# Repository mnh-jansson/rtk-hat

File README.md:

# RTK-HAT
Raspberry Pi compatible expansion board for RTK GNSS Module PX1125R

# About
**DISCLAIMER**

**Work In Progress**

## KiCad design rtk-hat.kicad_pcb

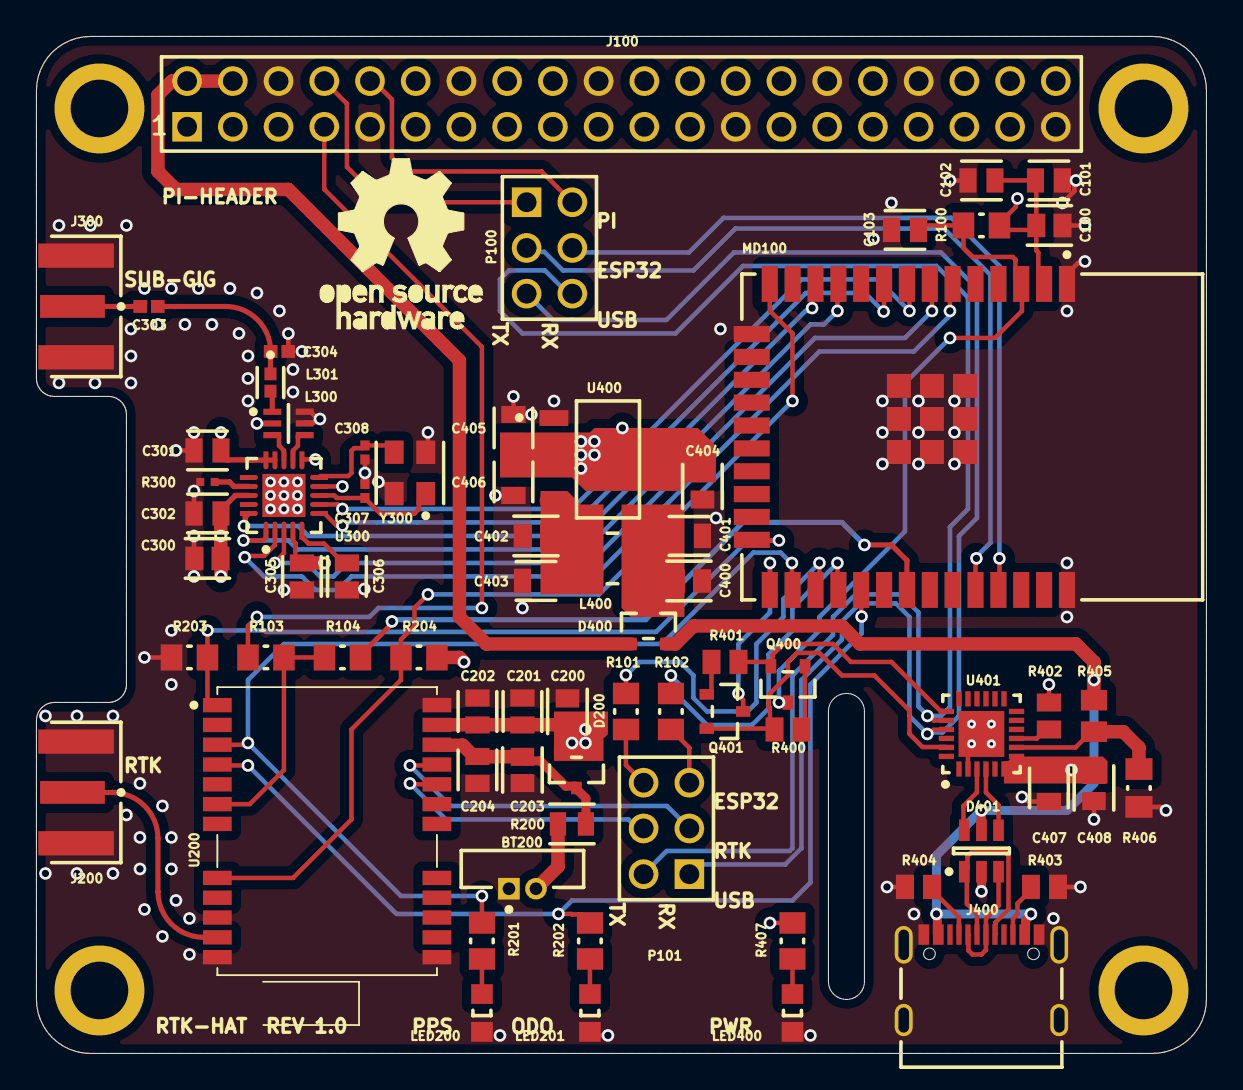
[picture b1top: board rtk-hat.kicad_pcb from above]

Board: 4 copper layers, 65.0 x 56.5 mm, 70 parts (0 on the bottom side), 60 nets.

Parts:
BT200: ML-621S/DN; FP-ML-621S-DN-MFG
C100, C200, C203, C300, C400, C402, C404, C408: GRM21BR61E106KA73L; FP-GRM21B-0_15-IPC_C
C101, C102, C103, C201, C202, C204, C301, C302, C305, C306, C401, C403, C405, C406, C407: C0805C104K5RACTU; FP-C0805C-DN-MFG
C303: GRM1555C1H101JA01D; CAPC1005X55X25ML05T10
C304: GRM1555C1H1R8CA01D; CAPC1005X55X25ML05T10
C307, C308: GRM1555C1H270JA01D; CAPC1005X55X25LL05T10
D200, D400: BAT54C,215; FP-SOT23-MFG
D401: USBLC6-2SC6; STM-SOT23-6L_V
J100: 61304021121
J200, J300: SMA-J-P-H-ST-EM1; FP-SMA-J-P-H-ST-EM1-MFG
J400: 629722000214
L300: 0896BM15A0001E; FP-0896BM15A0001E-MFG
L301: LQG15HN5N6S02D; FP-LQG15HH_02-IPC_A
L400: CBC3225T100MR; FP-CB3225-IPC_A
LED200, LED201, LED400: 150080RS75000; 0805_A
MD100: ESP32-WROOM-32; FP-ESP32-WROOM-32-MFG
P100, P101: 61300621121
Q400, Q401: SS8050-G; FP-SS8050-G-MFG
R100, R101, R102, R103, R104, R201, R202, R203, R204, R407: RC0805FR-071KL; RESC2013X60X35ML10T20
R200: CRGCQ0805F390R; FP-CRGCQ0805-IPC_C
R300: CRCW040256K0FKED; RESC1005X40X25LL05T05
R400, R401, R402, R403, R404: ERA6AEB512V; RESC2013X60X40LL20T25
R405: ERJ-6ENF2212V; RESC2013X70X40NL20T20
R406: CRCW080547K5FKEA; FP-CRCW0805-e3-IPC_A
U200: PX1125R
U300: CC1100ERTKR; FP-RTK0020B-MFG
U400: LDL1117S33R; FP-SOT223-0046067-IPC_C
U401: CP2102N-A01-GQFN24; SLAB-QFN-24-2550x2550TP_A_V
Y300: ABM8-26.000MHZ-10-1-U-T; FP-ABM8-MFG

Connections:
1PPS: MD100.26, R201.2, U200.3
+5V_PI: D400.1, J100.2, J100.4
BOOT_SEL: MD100.24, R203.2, U200.1
GND: BT200.1, C100.2, C101.1, C102.1, C103.2, C200.2, C201.1, C202.1, C203.2, C204.1, C300.2, C301.1, C302.1, C304.1, C305.1, C306.1, C307.1, C308.1, C400.2, C401.1, C402.2, C403.1, C404.2, C405.1, C406.1, C407.1, C408.2, D401.2, J100.6, J100.9, J100.14, J100.20, J100.25, J100.30, J100.34, J100.39, J200.2, J200.3, J200.4, J200.5, J300.2, J300.3, J300.4, J300.5, J400.A1/B12, J400.A12/B1, J400.Shell, L300.2, L300.5, L300.6, LED200.1, LED201.1, LED400.1, MD100.1, MD100.15, MD100.38, MD100.39, R203.1, R300.2, R403.1, R404.1, R406.1, U200.10, U200.12, U200.13, U200.24, U300.16, U300.19, U300.21, U400.1, U401.2, U401.25, Y300.2, Y300.4
NetBT200_2: BT200.2, R200.1
NetC103_1: C103.1, MD100.3, Q400.3, R100.1
NetC203_1: C203.1, C204.2, D200.3, R200.2, U200.22
NetC303_1: C303.1, J300.1
NetC303_2: C303.2, C304.2, L301.1
NetC306_2: C306.2, U300.5
NetC307_2: C307.2, U300.8, Y300.1
NetC308_2: C308.2, U300.10, Y300.3
NetC400_1: C400.1, C401.2, D400.3, L400.1
NetC402_1: C402.1, C403.2, L400.2, U400.3
NetD401_1: D401.1, J400.A6, J400.B6
NetD401_3: D401.3, J400.A7, J400.B7
NetD401_4: D401.4, U401.4
NetD401_6: D401.6, U401.3
NetJ100_7: J100.7, R103.1
NetJ100_8: J100.8, P100.1
NetJ100_10: J100.10, P100.2
NetJ200_1: J200.1, U200.11
NetJ400_A5: J400.A5, R404.2
NetJ400_B5: J400.B5, R403.2
NetL300_1: L300.1, L301.2
NetL300_3: L300.3, U300.13
NetL300_4: L300.4, U300.12
NetLED200_2: LED200.2, R201.1
NetLED201_2: LED201.2, R202.1
NetLED400_2: LED400.2, R407.1
NetMD100_6: MD100.6, U300.2
NetMD100_7: MD100.7, U300.3
NetMD100_8: MD100.8, U300.7
NetMD100_9: MD100.9, U300.6
NetMD100_11: MD100.11, U300.1
NetMD100_12: MD100.12, U300.20
NetMD100_25: MD100.25, Q401.3
NetMD100_27: MD100.27, R101.2
NetMD100_28: MD100.28, R102.2
NetMD100_31: MD100.31, R104.2
NetMD100_34: MD100.34, P100.3
NetMD100_35: MD100.35, P100.4
NetP100_5: P100.5, P101.1, U401.21
NetP100_6: P100.6, P101.2, U401.20
NetP101_5: P101.5, R102.1
NetP101_6: P101.6, R101.1
NetQ400_1: Q400.1, R400.1
NetQ400_2: Q400.2, R401.2, U401.19
NetQ401_1: Q401.1, R401.1
NetQ401_2: Q401.2, R400.2, U401.23
NetR300_1: R300.1, U300.17
NetR402_1: R402.1, U401.9
NetR405_1: R405.1, R406.2, U401.8
ODO: MD100.29, R202.2, U200.4
RSTN: MD100.14, R204.1, U200.8
RXD: P101.3, U200.21
RXD2: R103.2, R104.1, U200.6
TXD: P101.4, U200.20
VBUS: D400.2, D401.5, J400.A4/B9, J400.A9/B4, R405.2
VCC: C100.1, C101.2, C102.2, C200.1, C201.2, C202.2, C300.1, C301.2, C302.2, C305.2, C404.1, C405.2, C406.2, C407.2, C408.1, D200.1, D200.2, MD100.2, R100.2, R204.2, R402.2, R407.2, U200.23, U300.4, U300.9, U300.11, U300.14, U300.15, U300.18, U400.2, U400.4, U401.6, U401.7

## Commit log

2022-08-09 wip initial dump
